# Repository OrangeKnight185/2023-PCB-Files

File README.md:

# 2023-PCB-Files
The files for the Robosharks' on-board PCB for the MATE ROV 2023 season.

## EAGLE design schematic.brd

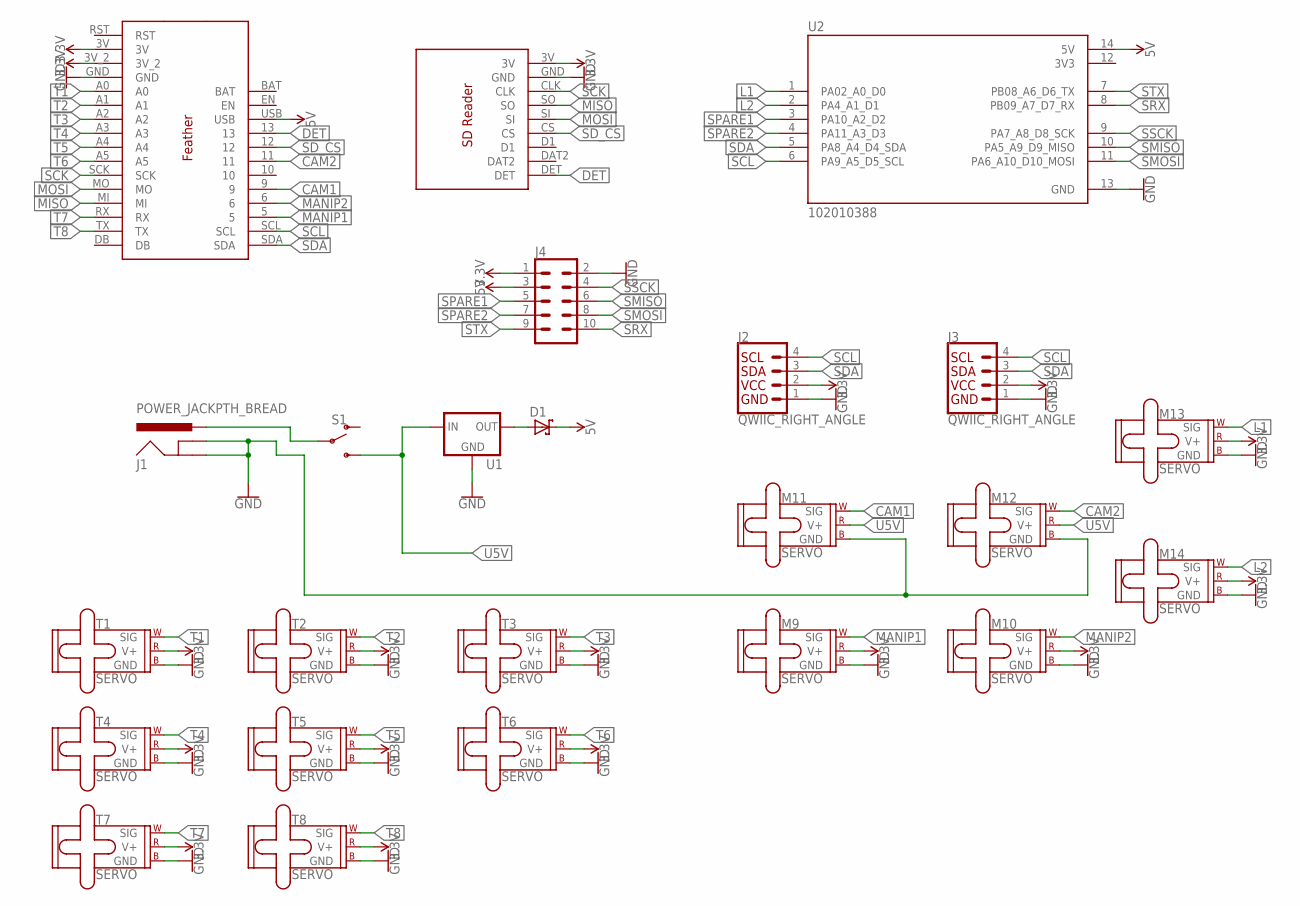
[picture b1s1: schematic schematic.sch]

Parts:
D1: SCHOTTKY-DIODEDO41; DO41-10
J1: POWER_JACKPTH_BREAD; POWER_JACK_PTH_BREAD
J2, J3: QWIIC_RIGHT_ANGLE; JST04_1MM_RA
J4: CONN_05X2PTH; 2X5
M9, M10, M11, M12, M13, M14: SERVO; 1X03
S1: SWITCH-SPDT-PTH-11.6X4.0MM; SWITCH_SPDT_PTH_11.6X4.0MM
T1, T2, T3, T4, T5, T6, T7, T8: SERVO; 1X03
U1: V_REG_78XXSIDE; 78XXL
U2: 102010388; MODULE_102010388
U$1: FEATHER
U$3: SD

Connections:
3.3V: J2.2, J3.2, J4.1, M9.2 (V+), M10.2 (V+), M13.2 (V+), M14.2 (V+), T1.2 (V+), T2.2 (V+), T3.2 (V+), T4.2 (V+), T5.2 (V+), T6.2 (V+), T7.2 (V+), T8.2 (V+), U$1.3V, U$1.3V_2, U$3.3V
3V3: U2.12 (3V3)
5V: D1.C, J4.3, U2.14 (5V), U$1.USB
CAM1: M11.1 (SIG), U$1.9
CAM2: M12.1 (SIG), U$1.11
DET: U$1.13, U$3.DET
GND: J1.GND, J1.GNDBREAK, J2.1, J3.1, J4.2, M9.3 (GND), M10.3 (GND), M11.3 (GND), M12.3 (GND), M13.3 (GND), M14.3 (GND), T1.3 (GND), T2.3 (GND), T3.3 (GND), T4.3 (GND), T5.3 (GND), T6.3 (GND), T7.3 (GND), T8.3 (GND), U1.GND, U2.13 (GND), U$1.GND, U$3.GND
L1: M13.1 (SIG), U2.1 (PA02_A0_D0)
L2: M14.1 (SIG), U2.2 (PA4_A1_D1)
MANIP1: M9.1 (SIG), U$1.5
MANIP2: M10.1 (SIG), U$1.6
MISO: U$1.MI, U$3.SO
MOSI: U$1.MO, U$3.SI
unnamed: J1.PWR, S1.2
unnamed: D1.A, U1.OUT
SCK: U$1.SCK, U$3.CLK
SCL: J2.4, J3.4, U2.6 (PA9_A5_D5_SCL), U$1.SCL
SDA: J2.3, J3.3, U2.5 (PA8_A4_D4_SDA), U$1.SDA
SD_CS: U$1.12, U$3.CS
SMISO: J4.6, U2.10 (PA5_A9_D9_MISO)
SMOSI: J4.8, U2.11 (PA6_A10_D10_MOSI)
SPARE1: J4.5, U2.3 (PA10_A2_D2)
SPARE2: J4.7, U2.4 (PA11_A3_D3)
SRX: J4.10, U2.8 (PB09_A7_D7_RX)
SSCK: J4.4, U2.9 (PA7_A8_D8_SCK)
STX: J4.9, U2.7 (PB08_A6_D6_TX)
T1: T1.1 (SIG), U$1.A0
T2: T2.1 (SIG), U$1.A1
T3: T3.1 (SIG), U$1.A2
T4: T4.1 (SIG), U$1.A3
T5: T5.1 (SIG), U$1.A4
T6: T6.1 (SIG), U$1.A5
T7: T7.1 (SIG), U$1.RX
T8: T8.1 (SIG), U$1.TX
U5V: M11.2 (V+), M12.2 (V+), S1.3 (S), U1.IN

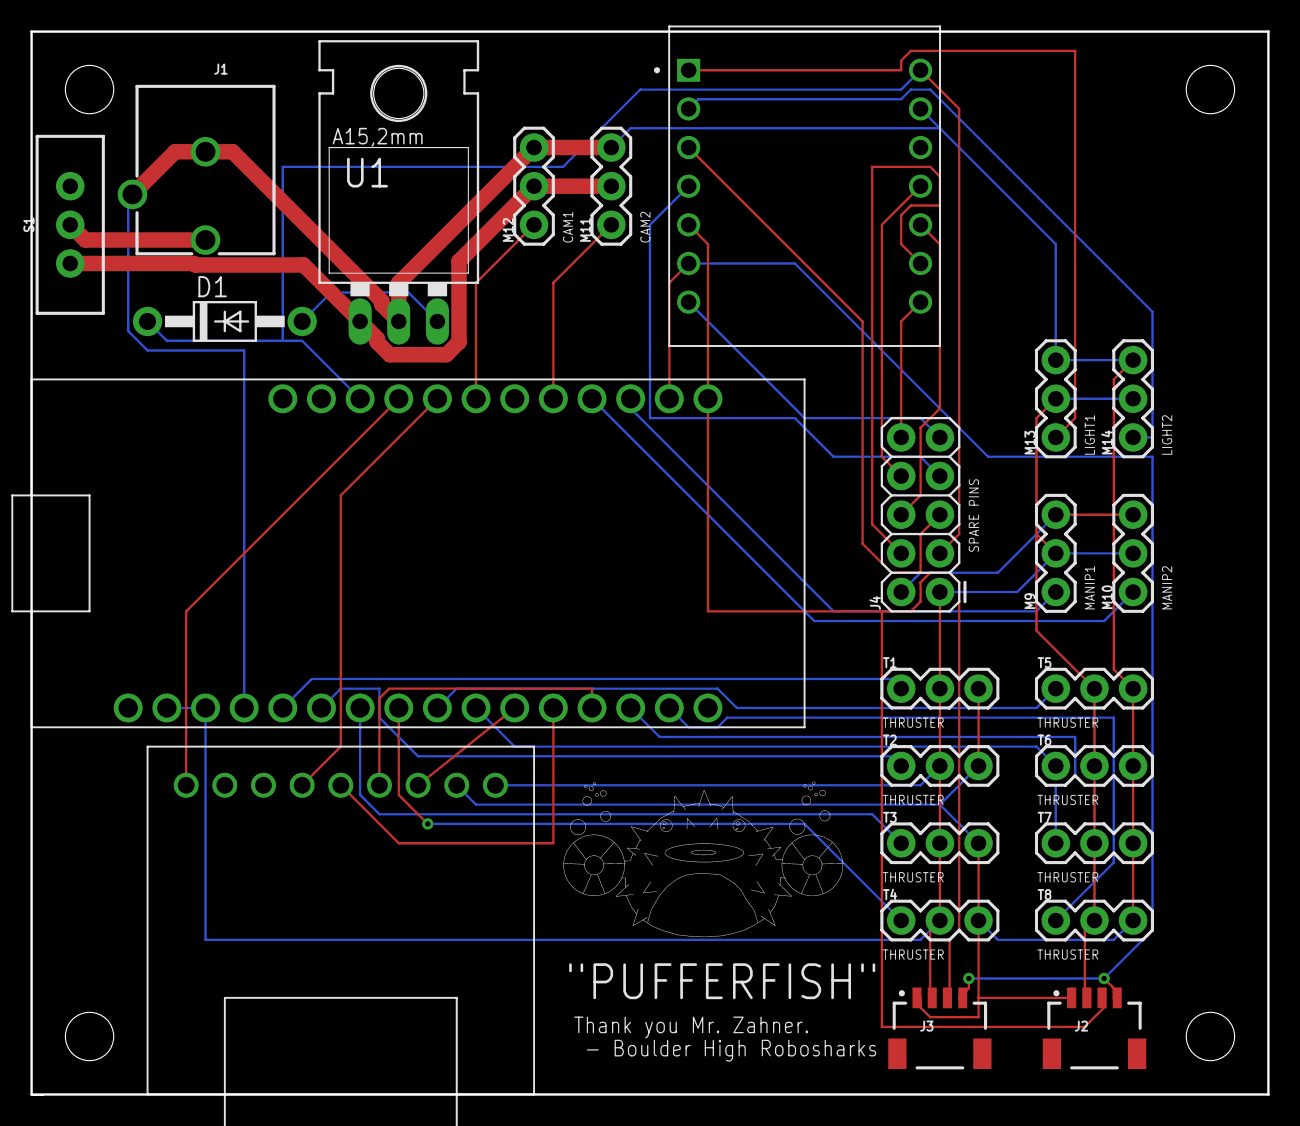
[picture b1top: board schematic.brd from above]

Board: 2 copper layers, 81.3 x 69.8 mm, 24 parts (0 on the bottom side), 34 nets.

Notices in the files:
parts and their libraries:
SparkFun-Connectors: Licensing: Creative Commons ShareAlike 4.0 International - https://creativecommons.org/licenses/by-sa/4.0
